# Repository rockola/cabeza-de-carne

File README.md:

# cabeza-de-carne
Yet another Meathead clone

* v0.1: initial import, complete, unverified
* v0.2: more compact board, 3mm LED
* v0.3: longer footprint for D2 (not standing anymore), fixed silkscreen for Q2 (had wrong markings for B,C), verified

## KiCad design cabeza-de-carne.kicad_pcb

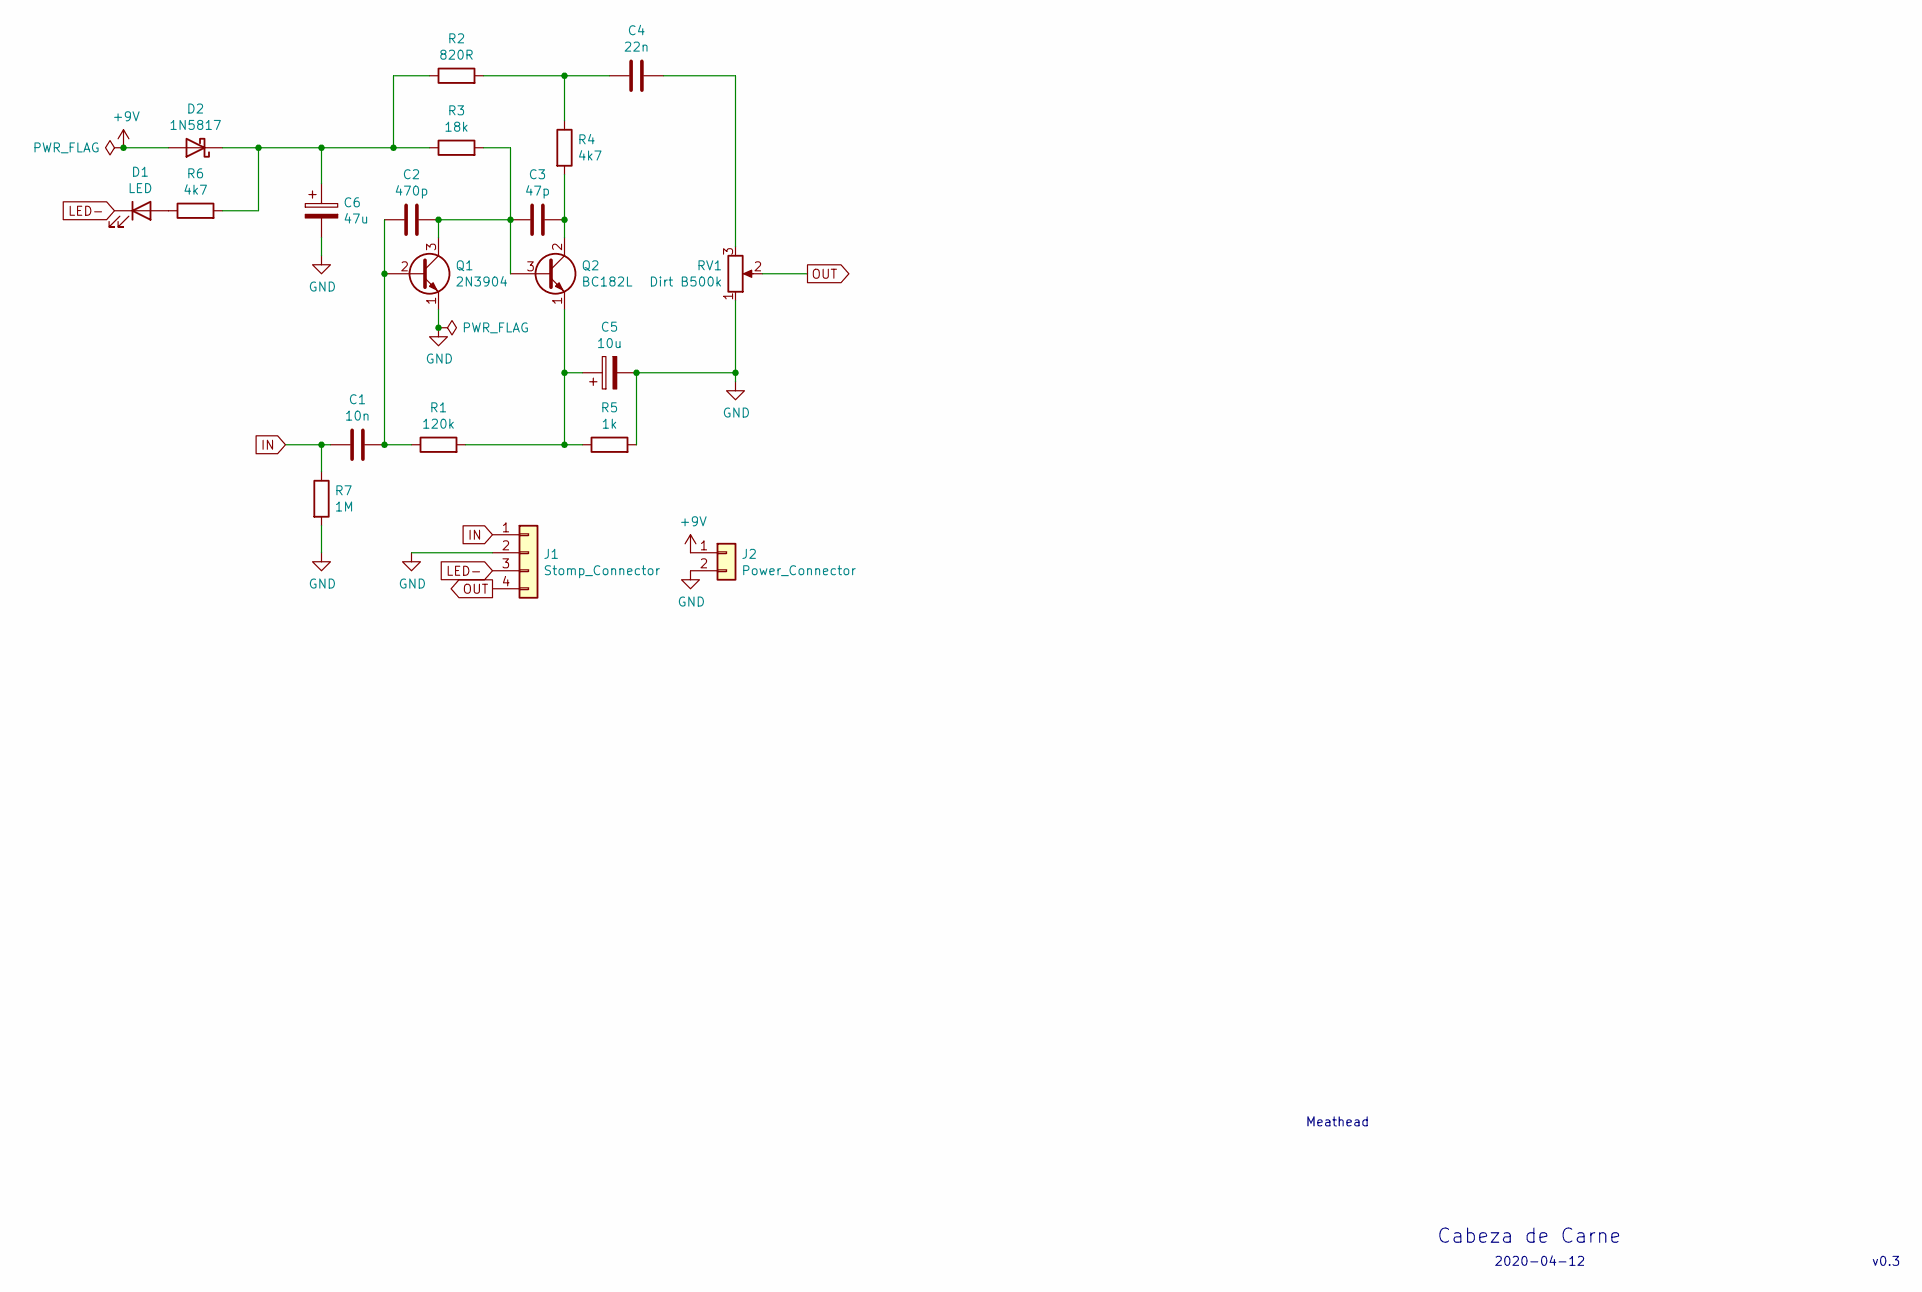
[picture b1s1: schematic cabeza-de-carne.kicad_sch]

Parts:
C1: 10n; C_Rect_L7.0mm_W2.5mm_P5.00mm
C2: 470p; C_Disc_D5.0mm_W2.5mm_P5.00mm
C3: 47p; C_Disc_D5.0mm_W2.5mm_P5.00mm
C4: 22n; C_Rect_L7.0mm_W2.5mm_P5.00mm
C5: 10u; CP_Radial_D5.0mm_P2.50mm
C6: 47u; CP_Radial_D5.0mm_P2.50mm
D1: LED; LED_D3.0mm
D2: 1N5817; DO41-3
J1: Stomp_Connector; Stomp_4pin
J2: Power_Connector; Power_Header_2pin_TOP
Q1: 2N3904; TO92_EBC
Q2: BC182L; TO92_ECBE
R1: 120k; R_Axial_DIN0207_L6.3mm_D2.5mm_P7.62mm_Horizontal
R2: 820R; R_Axial_DIN0207_L6.3mm_D2.5mm_P7.62mm_Horizontal
R3: 18k; R_Axial_DIN0207_L6.3mm_D2.5mm_P7.62mm_Horizontal
R4, R6: 4k7; R_Axial_DIN0207_L6.3mm_D2.5mm_P7.62mm_Horizontal
R5: 1k; R_Axial_DIN0207_L6.3mm_D2.5mm_P7.62mm_Horizontal
R7: 1M; R_Axial_DIN0207_L6.3mm_D2.5mm_P7.62mm_Horizontal
RV1: Dirt B500k; 16mm_BoardMount

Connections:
+9V: D2.2 (A), J2.1 (PWR)
GND: C5.2, C6.2, J1.2 (GND), J2.2 (GND), Q1.1 (E), R5.2, R7.2, RV1.1
IN: C1.1, J1.1 (IN), R7.1
LED-: D1.1 (K), J1.3 (SW)
unnamed: C1.2, C2.1, Q1.2 (B), R1.1
unnamed: C2.2, C3.1, Q1.3 (C), Q2.3 (B), R3.2
unnamed: C3.2, Q2.2 (C), R4.2
unnamed: C4.1, R2.2, R4.1
unnamed: C4.2, RV1.3
unnamed: C5.1, Q2.1 (E), R1.2, R5.1
unnamed: C6.1, D2.1 (K), R2.1, R3.1, R6.2
unnamed: D1.2 (A), R6.1
OUT: J1.4 (OUT), RV1.2

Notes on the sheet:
v0.3
2020-04-12
Cabeza de Carne
Meathead

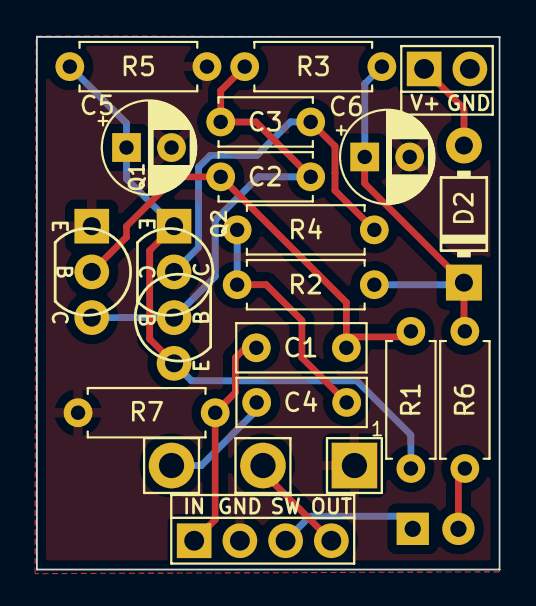
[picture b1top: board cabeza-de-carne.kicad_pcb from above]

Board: 2 copper layers, 25.7 x 29.6 mm, 20 parts (1 on the bottom side), 13 nets.

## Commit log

2020-03-12 initial Gerbers
2020-03-12 initial image versions
2020-03-12 MIT license
2020-03-12 initial
2020-03-13 0.2: more compact board
2020-04-12 v0.3: longer footprint for D1 (not standing anymore), fixed silkscreen for Q2 (had wrong markings for B,C)
2020-04-12 v0.3 gerbers, images
2020-08-01 Update README.md
    Verification build was done a while ago
2022-01-11 ignore backups directory
2022-01-11 updated to KiCad 6.0
